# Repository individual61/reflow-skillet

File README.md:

# reflow-skillet

A reflow oven based on a cheap Target skillet, with OLED display screen and thermocouple input. Now on a custom PCB.

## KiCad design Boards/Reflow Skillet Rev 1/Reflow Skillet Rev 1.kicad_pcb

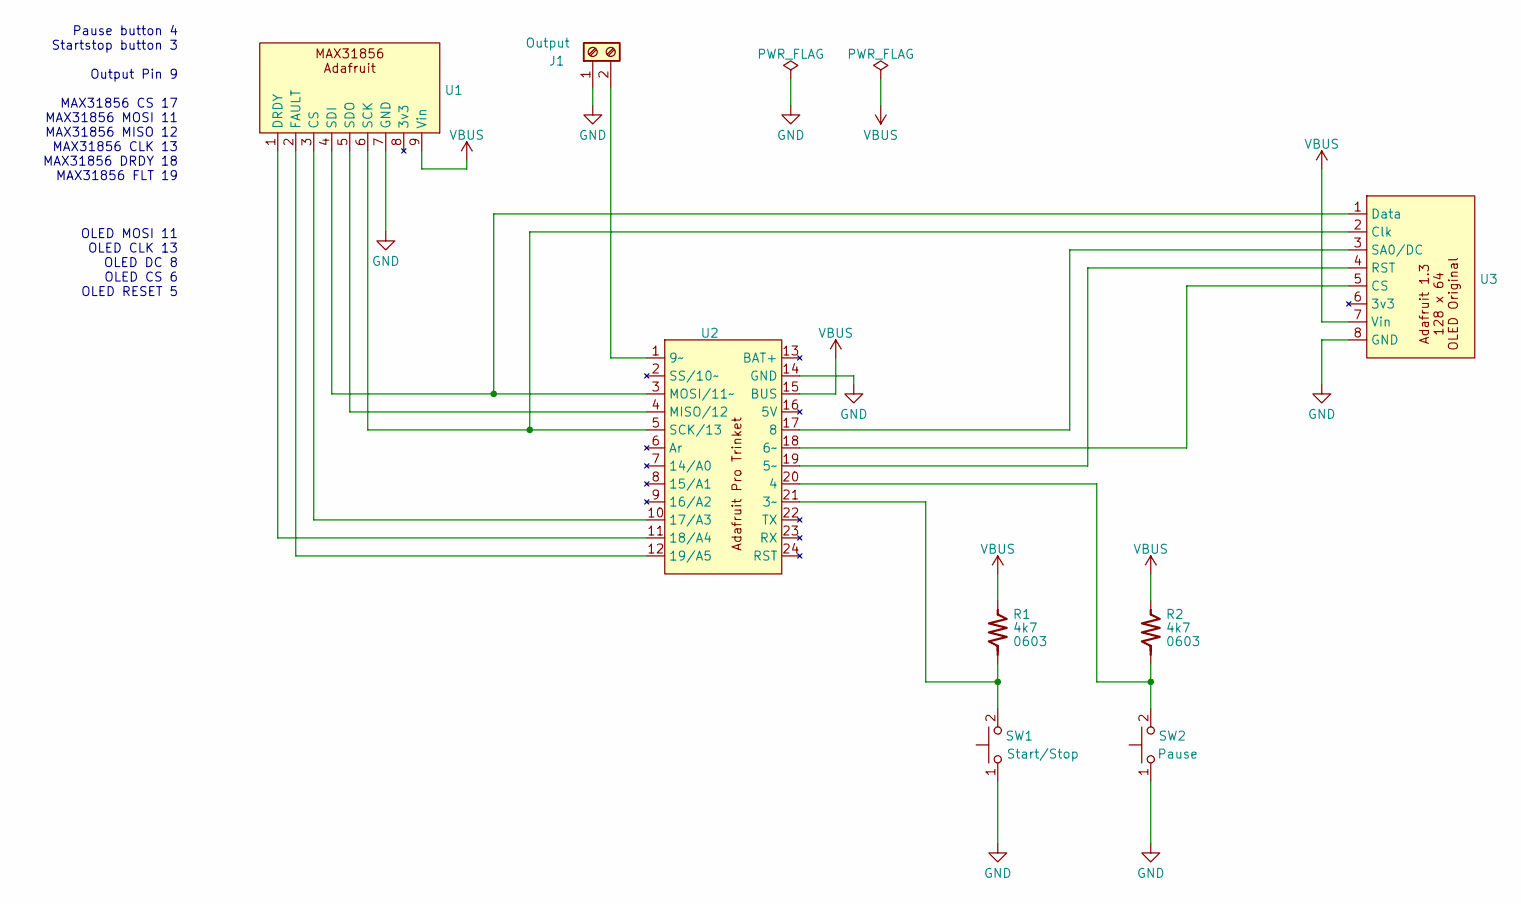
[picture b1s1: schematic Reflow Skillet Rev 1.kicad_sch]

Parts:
J1: Output; TerminalBlock_TE_282834-2_1x02_P2.54mm_Horizontal; MFR PN 282834-2; DIGIKEY PN A98333-ND
R1, R2: 4k7; R_0603_1608Metric_Pad0.98x0.95mm_HandSolder; MPN MFR P/N
SW1: Start/Stop; SW_TH_Tactile_Omron_B3F-10xx
SW2: Pause; SW_TH_Tactile_Omron_B3F-10xx
U1: Adafruit MAX31856
U2: Adafruit Pro Trinket
U3: Adafruit 1.3 128 x 64 OLED Original

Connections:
GND: J1.1, SW1.1, SW2.1, U1.7 (GND), U2.14 (GND), U3.8 (GND)
unnamed: J1.2, U2.1 (9~)
unnamed: U1.3 (CS), U2.10 (17/A3)
unnamed: U1.1 (DRDY), U2.11 (18/A4)
unnamed: U1.2 (FAULT), U2.12 (19/A5)
unnamed: U1.6 (SCK), U2.5 (SCK/13), U3.2 (Clk)
unnamed: U1.4 (SDI), U2.3 (MOSI/11~), U3.1 (Data)
unnamed: U1.5 (SDO), U2.4 (MISO/12)
unnamed: R1.2, SW1.2, U2.21 (3~)
unnamed: R2.2, SW2.2, U2.20 (4)
unnamed: U2.19 (5~), U3.4 (RST)
unnamed: U2.18 (6~), U3.5 (CS)
unnamed: U2.17 (8), U3.3 (SA0/DC)
VBUS: R1.1, R2.1, U1.9 (Vin), U2.15 (BUS), U3.7 (Vin)

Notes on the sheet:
Pause button 4 Startstop button 3 Output Pin 9 MAX31856 CS 17 MAX31856 MOSI 11 MAX31856 MISO 12 MAX31856 CLK 13 MAX31856 DRDY 18 MAX31856 FLT 19 OLED MOSI 11 OLED CLK 13 OLED DC 8 OLED CS 6 OLED RESET 5

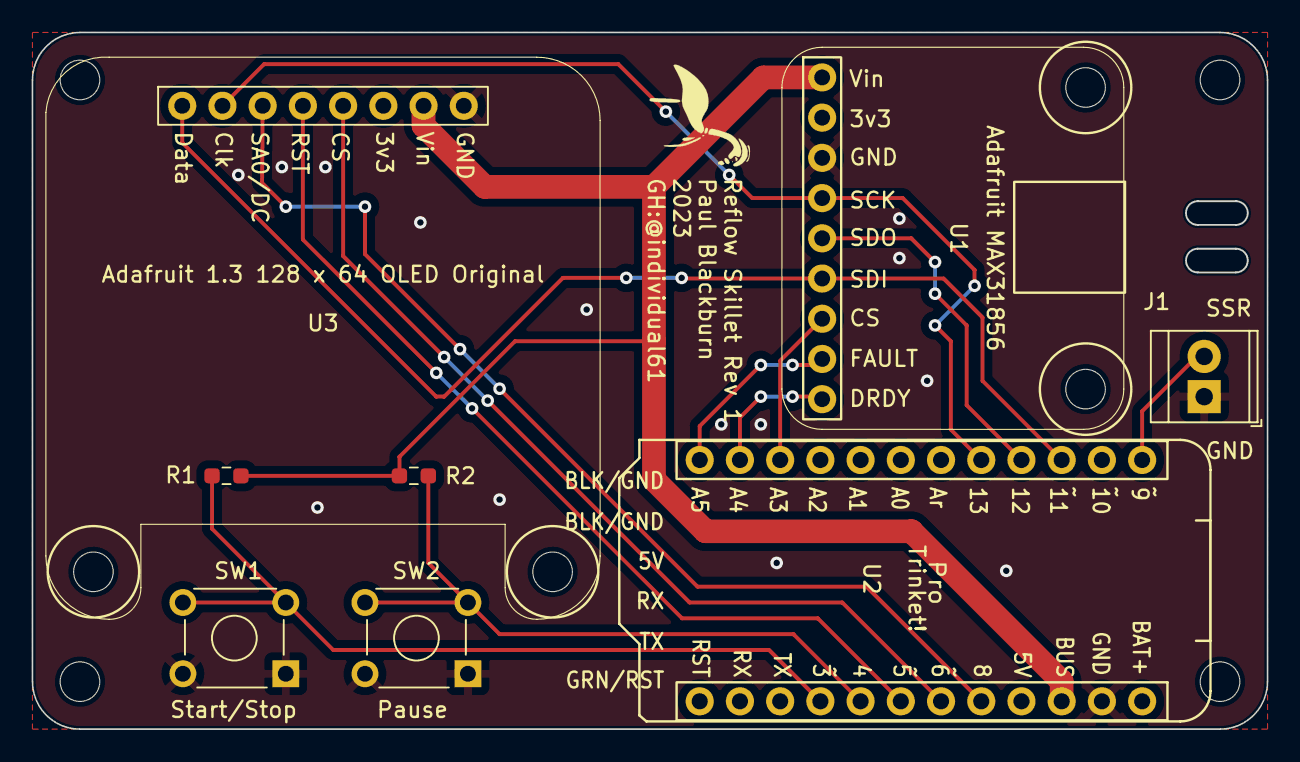
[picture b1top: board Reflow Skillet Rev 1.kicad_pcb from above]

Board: 2 copper layers, 78.0 x 44.0 mm, 8 parts (0 on the bottom side), 14 nets.

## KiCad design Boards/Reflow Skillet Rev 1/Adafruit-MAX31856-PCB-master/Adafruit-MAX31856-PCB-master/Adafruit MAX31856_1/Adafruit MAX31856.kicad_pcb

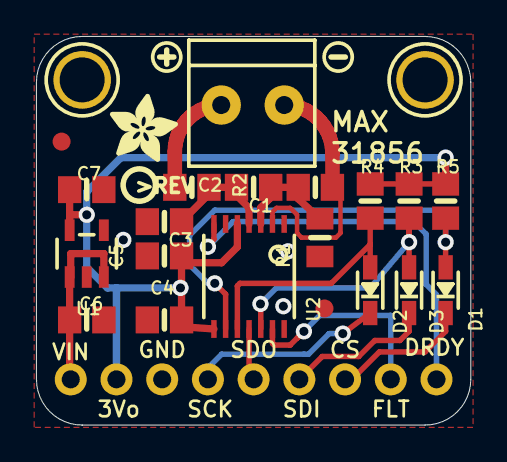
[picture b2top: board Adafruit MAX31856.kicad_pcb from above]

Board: 2 copper layers, 24.1 x 21.6 mm, 28 parts (1 on the bottom side), 16 nets.

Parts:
C1: 0.01uF; 0805_10MGAP
C2, C4, C5: 0.1uF; 0805-NO
C3: 0.01uF; 0805-NO
C6, C7: 10uF; 0805-NO
D1, D2, D3: 1N4148; SOD-323
FID1, FID2: FIDUCIAL""; FIDUCIAL_1MM
JP1: 1X09_ROUND_70
R1, R2: 100; 0805-NO
R3, R4, R5: 10K; 0805-NO
U1: mic5225-3.3; SOT23-5
U2: MAX31856; TSSOP14
U$1: PCBFEAT-REV-040
U$13, U$14: MOUNTINGHOLE2.5; MOUNTINGHOLE_2.5_PLATED
U$23: SYMBOL_PLUS
U$24: SYMBOL_MINUS
U$25: ADAFRUIT_3.5MM
U$26: ADAFRUIT_TEXT_20MM
X1: 3.5mm term; TERMBLOCK_1X2-3.5MM

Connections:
3.3V: C4.1, C5.1, C7.1, JP1.8, R3.2, R4.2, R5.2, U1.5, U2.5, U2.8
DRDY: JP1.1, U2.7
GND: C1.1, C3.2, C4.2, C5.2, C6.2, C7.2, JP1.7, U1.2, U2.1, U2.14
SCK: D2.C, JP1.6
SCK_3V: D2.A, R4.1, U2.10
SDI: D3.C, JP1.4
SDO: JP1.5, U2.11
SDO_3V: D3.A, R3.1, U2.12
T+: C2.2, C3.1, R2.2, U2.4
T-: C1.2, C2.1, R1.2, U2.3
THERM+: R2.1, X1.1
THERM-: R1.1, U2.2, X1.2
VIN: C6.1, JP1.9, U1.1, U1.3
~CS_3V: D1.A, R5.1, U2.9
~CS: D1.C, JP1.3
~FAULT: JP1.2, U2.13

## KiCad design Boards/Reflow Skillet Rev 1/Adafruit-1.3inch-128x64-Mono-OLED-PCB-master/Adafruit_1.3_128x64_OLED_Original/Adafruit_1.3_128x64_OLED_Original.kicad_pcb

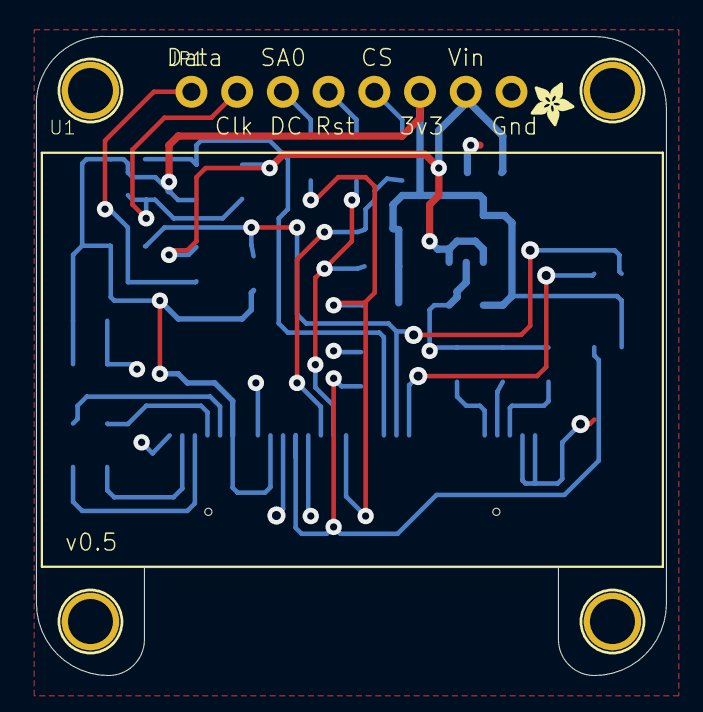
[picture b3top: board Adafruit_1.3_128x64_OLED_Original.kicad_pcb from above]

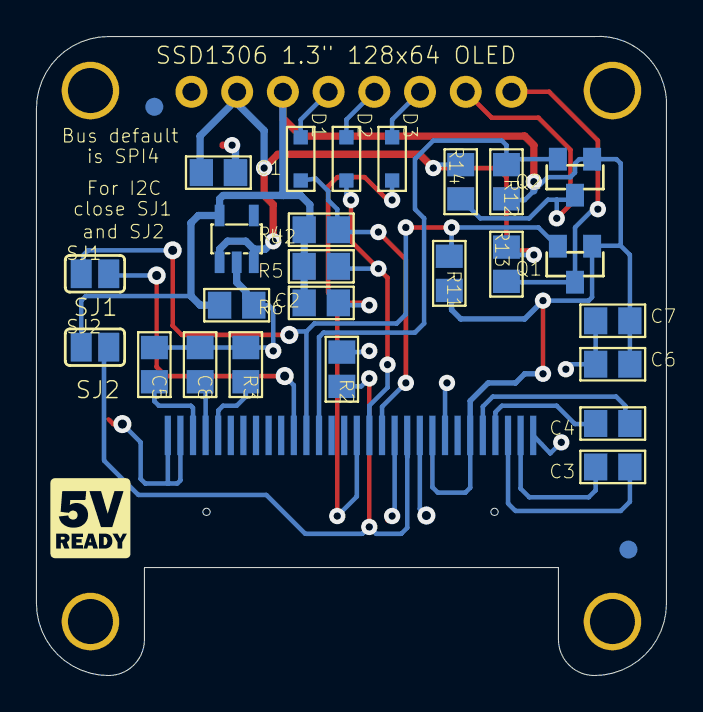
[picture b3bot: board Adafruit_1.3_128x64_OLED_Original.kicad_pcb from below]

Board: 2 copper layers, 35.0 x 35.5 mm, 35 parts (28 on the bottom side), 22 nets.

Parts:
C1, C2, C5: 10uF; 0805
C3, C4, C6, C7, C8: 2.2uF; 0805
D1, D2, D3: 1N4148; SOD-323
FID1, FID2: FIDUCIAL""; FIDUCIAL_1MM
JP1: 1X08_ROUND_70
Q1, Q2: BSS138; SOT23-WIDE
R2, R4, R5, R6, R11, R12, R13, R14: 10K; 0805
R3: 390K; 0805
SJ1, SJ2: SOLDERJUMPER_REFLOW_NOPASTE
U1: UG-2864HSWEG01; UG-2864HSWEG01_1.3_WRAPAROUND
U2: SOT23-5
U$23, U$24, U$25, U$26: MOUNTINGHOLE2.5; MOUNTINGHOLE_2.5_PLATED
U$27: ADAFRUIT_2.5MM
U$28: LOGIC_5VREADY_5MM

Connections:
3.3V: C2.1, C6.2, C7.2, JP1.6, Q1.1, Q2.1, R4.2, R5.2, R6.2, R11.2, R12.2, SJ2.1, U1.6, U1.9, U2.5
CS_3.3V: D1.A, R4.1, U1.13
CS_5.0V: D1.C, JP1.5
D0/SCLK/SCK_3.3V: Q2.2, R12.1, U1.18
D0/SCLK/SCK_5.0V: JP1.2, Q2.3, R14.1
D1/MOSI/SDA1_3.3V: Q1.2, R11.1, SJ1.1, U1.19
D1/MOSI/SDA_5.0V: JP1.1, Q1.3, R13.1
DC/SA0_3.3V: D3.A, R6.1, U1.15
DC/SA0_5.0V: D3.C, JP1.3
GND: C1.2, C2.2, C5.1, C6.1, C7.1, C8.1, JP1.8, R2.1, R3.1, U1.1, U1.8, U1.10, U1.12, U1.29, U1.30, U2.2
unnamed: R2.2, SJ2.2, U1.11
unnamed: SJ1.2, U1.20
unnamed: R3.2, U1.26
unnamed: C3.2, U1.2
unnamed: C3.1, U1.3
unnamed: C4.2, U1.4
unnamed: C4.1, U1.5
unnamed: C5.2, U1.28
unnamed: C8.2, U1.27
RST_3.3V: D2.A, R5.1, U1.14
RST_5.0V: D2.C, JP1.4
VIN: C1.1, JP1.7, R13.2, R14.2, U2.1, U2.3

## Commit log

2018-04-10 Initial commit
    Initial commit.
2018-04-20 Adafruit Example is working
    Implemented Adafruit's example. Reads back CJ temp and Th temp. Reports faults. Serial. Uses software SPI pins.
2018-05-02 Added OLED test code
    OLED is wired up and runs the Adafruit test code!
2018-05-04 Basic screen support, fault detection
    Implemented state machine with idle, running, fault.
    Faults are apparently reset by power cycling device. Not sure if this is an issue with my program or not.
2018-05-04 Created temp, display and button files
    Split code across temp, display, and button C++/header files.
    Added parameters.h as common header.
2018-05-05 Sketched button actions
    Buttons are Start/Stop and Pause/Unpause. Added placeholders for transition functions.
2018-05-06 Fixing mangled files
    Somehow (Atom? Platformio?) an awful chimera of main.cpp and parameters.h was created, and I have no idea why.
    First attempt at fixing. Only compile error is the Config() member of the thermocouple Adafruit library. Had to make a modification to avoid the 250 ms delay per read (!).
2018-05-07 Moved Adafruit MAX31856 library to project folder
    Couldn't get Platformio to use both the modified source and h files, so I removed the library from platformio.ini and moved them to the project folder.
2018-05-07 Finished reworking temp query delay
    Querying temperature is now < 1 ms and is done every N ms.
    Added dot in lower right to indicate each run through loop().
    Fixed display size issue by editing the library header again (for some reason this works, when for the temperature library it seems that the header file I edited was not being used).
    Fixed running/paused/idle transitions.
2018-05-07 Working on Profile routines
    Atom or PlatformIO took a shit all over parameters.h again, replacing its contents with that of main.cpp. Checking this in before it causes more havoc.
2018-05-07 Fixed most of the overwriting problem
2018-05-07 Basic profile functionality completed
2018-05-08 Added heating indicator
    And made it purty.
2018-05-09 Temp commit
    Before Atom takes YET ANOTHER SHIT ALL OVER MY FILES.
    This time it put half of parameters.h into two files. Good job.
2018-05-09 Adding PID
    Adding PID. Incomplete. Testing.
2018-05-15 Adding source files for PID library
    Wasn't successful editing PlatformIO libraries at the origin, and the PID library doesn't seem to have a straightforward reset function.
2018-05-16 WHAT THE FUCK, GODDAMNIT ATOM
2018-05-16 First compile after Atom took a shit all over everything
2018-05-16 Another stupid commit because Atom sucks
2018-05-17 Fixed a few things
    Output not turning off after going to Idle,
    Time remaining was counting (number of steps) times (first step time)
    etc
2018-05-17 First successful run
2018-05-19 In process
2018-05-19 Lots of code refactoriing, temp ramp
    Tidied up code, moved to a two-array solution for profile temp and times, implemented linear ramps
2018-05-19 Got profile working except for last step
2018-05-19 Adjusted display step count
2018-05-20 Tuning PID
    Definitely not there yet
2018-05-20 First good PID test
    Setpoint 100 deg C, was stable. Lid on.
2018-05-20 First reflow test
    On a perf board
2018-05-21 Removed serial output for plotting
    Version as used to reflow POV Stick 5050 Rev A #1
2020-09-20 Tidying up
2023-05-12 Right before changes to address screen glitch.
2023-05-16 Finally fixed, modified profile for low temp solder
2023-05-31 Making a carrier board
2023-06-01 Board before routing
2023-06-01 As sent to jlcpcb
